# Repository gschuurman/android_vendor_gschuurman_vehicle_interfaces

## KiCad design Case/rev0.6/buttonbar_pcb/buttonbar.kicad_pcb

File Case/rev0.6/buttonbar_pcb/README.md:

# Button bar PCB (case rev 0.6)

Small 2-layer board (176.7 x 11.5 mm) that sits behind the 9 caps of the case's button bar.
Everything goes over the existing **J12** connector on the rev 0.6 main board (5 wires, no main-board change).

Files: `buttonbar.kicad_pro/.kicad_sch/.kicad_pcb` (open in KiCad 7 or newer), project footprint
library `buttonbar.pretty` (all footprints included, no global libraries needed), `buttonbar_schematic.pdf`,
`gerbers/` + `buttonbar_gerbers.zip` (JLCPCB-ready, 2 layers, 1.6 mm), `render/`, `scripts/` (generators).

Status: schematic netlist matches the PCB 1:1 (10 nets), KiCad DRC 0 errors, 0 warnings, 0 unconnected.

## How it works (diode coding)

Every J12 line has a 1k series resistor, a 10k pull-up and 100 nF on the main board.
Single buttons short one line to GND. Combo buttons pull two lines low through two BAT85 Schottky diodes.

| Button | J12 lines low |
|---|---|
| Screen off | 1 (S, GPIO18) |
| Vol + | 2 (U, GPIO17) |
| Vol - | 3 (D, GPIO22) |
| Mute | 4 (M, GPIO16) |
| Play/Pause | 2 + 3 |
| Prev | 3 + 4 |
| Next | 2 + 4 |
| Home | 1 + 3 |
| Voice | 1 + 2 |
| (spare code) | 1 + 4 |

Firmware: wait ~30 ms after the first line goes low, then read all four lines and decode the pattern.
The current firmware treats the lines as four separate buttons, so it needs this decode step.

## Build notes

- **BAT85 (or BAT43) only.** A 1N4148 leaves the line at about 0.8 V, right at the RP2350 VIL limit.
  The cathode band goes on the pad marked K (the square pad).
- **Switch pitch is assumed** at 5.08 mm, 2 pins, body 6 x 3.5 mm, 5 mm high (KW-1556 / Adafruit 1489 type; no
  drawing could be downloaded). Measure yours before ordering. If they differ, change the footprint in
  `buttonbar.pretty` and `btn_total_h` / `btn_body` in the case.
- **J1 = J12 pin for pin** (1 S, 2 U, 3 D, 4 M, 5 GND). There is only 3 mm behind the board in the bar,
  so a pin header does not fit: solder the 5 wires straight into the J1 pads from the back and run them
  out through the wire slot in the bar's back wall (case updated: slot now x -17..-5, support rib moved to x -24
  so it clears J1).
- Switches, diodes and labels are on the front (F) side; solder from the back.
- It needs both copper layers. A single-sided version could not be routed without wire links, so on perfboard
  treat the red (F.Cu) tracks as wire links.

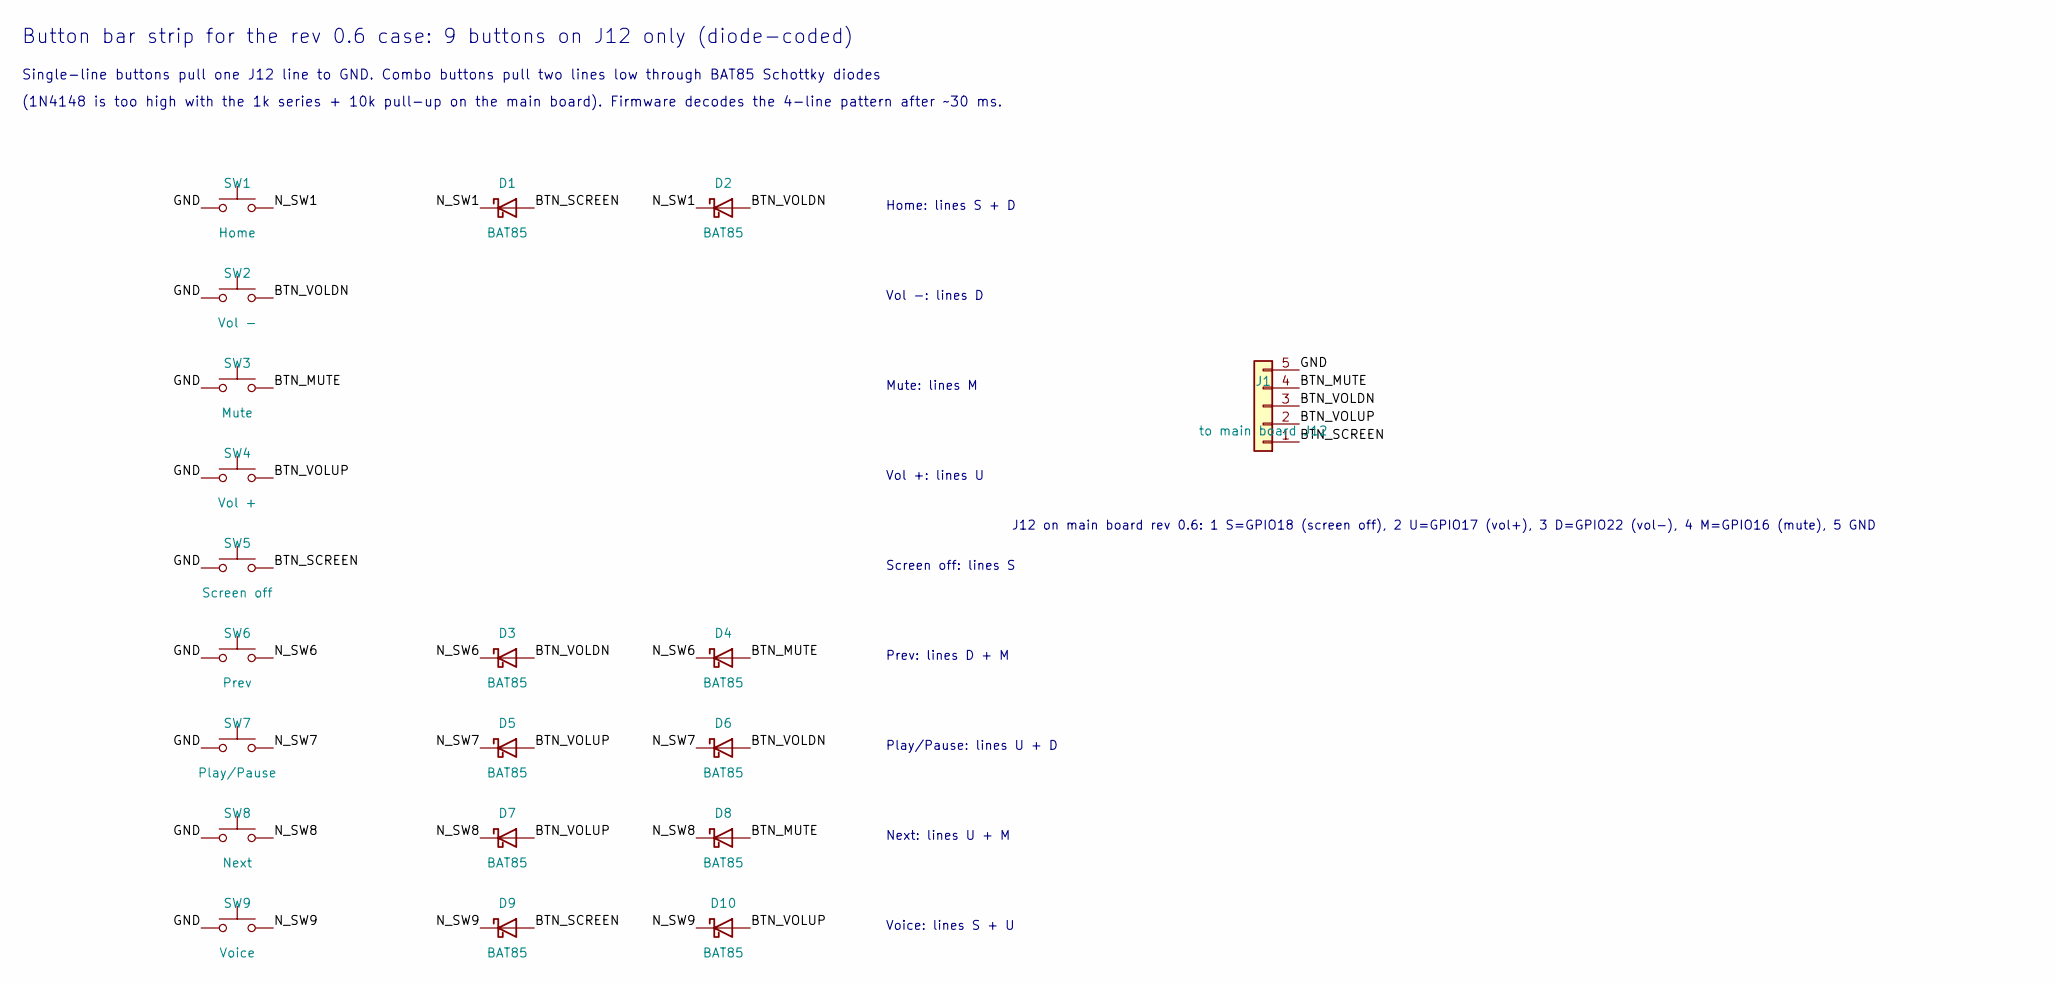
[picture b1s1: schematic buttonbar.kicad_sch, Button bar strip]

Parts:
D1, D2, D3, D4, D5, D6, D7, D8, D9, D10: BAT85; D_DO-34_SOD68_P7.62mm_Horizontal
J1: to main board J12; PinHeader_1x05_P2.54mm_Vertical
SW1: Home; SW_Tactile_6x3.5mm_2pin_P5.08mm
SW2: Vol -; SW_Tactile_6x3.5mm_2pin_P5.08mm
SW3: Mute; SW_Tactile_6x3.5mm_2pin_P5.08mm
SW4: Vol +; SW_Tactile_6x3.5mm_2pin_P5.08mm
SW5: Screen off; SW_Tactile_6x3.5mm_2pin_P5.08mm
SW6: Prev; SW_Tactile_6x3.5mm_2pin_P5.08mm
SW7: Play/Pause; SW_Tactile_6x3.5mm_2pin_P5.08mm
SW8: Next; SW_Tactile_6x3.5mm_2pin_P5.08mm
SW9: Voice; SW_Tactile_6x3.5mm_2pin_P5.08mm

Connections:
/BTN_MUTE: D4.2 (A), D8.2 (A), J1.4, SW3.2
/BTN_SCREEN: D1.2 (A), D9.2 (A), J1.1, SW5.2
/BTN_VOLDN: D2.2 (A), D3.2 (A), D6.2 (A), J1.3, SW2.2
/BTN_VOLUP: D5.2 (A), D7.2 (A), D10.2 (A), J1.2, SW4.2
/N_SW1: D1.1 (K), D2.1 (K), SW1.2
/N_SW6: D3.1 (K), D4.1 (K), SW6.2
/N_SW7: D5.1 (K), D6.1 (K), SW7.2
/N_SW8: D7.1 (K), D8.1 (K), SW8.2
/N_SW9: D9.1 (K), D10.1 (K), SW9.2
GND: J1.5, SW1.1, SW2.1, SW3.1, SW4.1, SW5.1, SW6.1, SW7.1, SW8.1, SW9.1

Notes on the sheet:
Button bar strip for the rev 0.6 case: 9 buttons on J12 only (diode-coded)
Single-line buttons pull one J12 line to GND. Combo buttons pull two lines low through BAT85 Schottky diodes
(1N4148 is too high with the 1k series + 10k pull-up on the main board). Firmware decodes the 4-line pattern after ~30 ms.
Home: lines S + D
Vol -: lines D
Mute: lines M
Vol +: lines U
Screen off: lines S
Prev: lines D + M
Play/Pause: lines U + D
Next: lines U + M
Voice: lines S + U
J12 on main board rev 0.6: 1 S=GPIO18 (screen off), 2 U=GPIO17 (vol+), 3 D=GPIO22 (vol-), 4 M=GPIO16 (mute), 5 GND

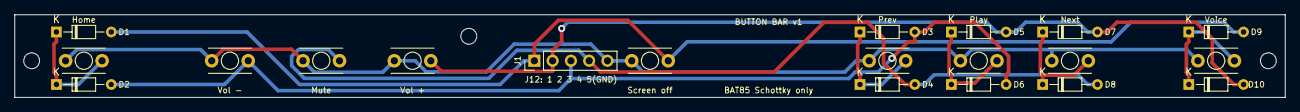
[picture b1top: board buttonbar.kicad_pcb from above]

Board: 2 copper layers, 176.7 x 11.5 mm, 23 parts (0 on the bottom side), 10 nets.

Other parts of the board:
H1, H2, H3: M2 hole; MountingHole_2.2mm_M2

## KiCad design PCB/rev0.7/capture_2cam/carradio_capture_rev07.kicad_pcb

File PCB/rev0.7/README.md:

# PCB rev 0.7: two-camera capture

Rev 0.7 only changes the USB module and adds a capture module, in two versions: `capture_1cam/` (one camera)
and `capture_2cam/` (two cameras). Both plug into the same J29 socket on the USB module; build one of them. The main, audio and
GNSS boards stay at rev 0.6.

## Two-camera capture module (`capture_2cam/`)

Two MacroSilicon MS2107 (LCSC C42374499, LQFP-48), one per camera: analog CVBS in, USB 2.0 UVC out,
behind a CH334R 4-port hub (U10, C4154405) so both share the USB module's single J29 port. Android sees two
normal external cameras (default VID:PID 534d:0021 each), so no driver is needed. The RearViewCamera app
currently opens the first external camera; it needs a setting (or a USB-path match) to pick the reverse one.

- 36 x 67.5 mm, 2 layers. Same outline and H1 as the USB module, extended 12.5 mm downward to the main board's
  bottom edge (the USB module's right edge is already the main board edge).
- J1 (CAM1) and J101 (CAM2): JST PH 2-pin video in (1 = CVBS, 2 = GND), each with 75 ohm termination, 47 nF
  coupling and a USBLC6 ESD clamp.
- J2: 2x3 2.54 mm male header on the bottom side, plugs into USB module J29 and feeds the hub upstream.
- Hub port 1 camera 1, port 2 camera 2, port 3 to J3 (1x4 pads, not fitted: 5 V, D-, D+, GND) for an
  optional third capture board or a test device, port 4 unused.
- Each channel: 12 MHz crystal, internal LDOs, status LED (D1/D101). EEPROMs U3/U103 and R5/R105 are DNP and
  sit on the underside; fit one only to give a camera its own USB name/IDs (ms-tools).
- Routed, DRC 0 unconnected, no copper errors (silkscreen warnings only; H1 is a board-only part).
- Each camera's own 12 V still comes from the reverse-lamp (or other) feed, not from this board.

### How many cameras

Each MS2107 sends uncompressed YUV, about 21 MB/s per PAL/NTSC camera. Everything shares the VIM3 header's
single USB 2.0 High Speed link, which can reserve about 48 MB/s for video, so two cameras can stream at once
(about 41 MB/s) with the RTL-SDR (about 5 MB/s, bulk) still fitting. A third camera on J3 only works if it does
not stream at the same time as the other two. These are calculated numbers, not measured.

### USB pair lengths (mm)

| Pair | D+ | D- |
|---|---|---|
| J2 to hub (upstream; D+ hand-routed on B.Cu between the J2 GND pins) | 12.6 | 10.4 |
| hub to camera 1 | 33.1 | 32.3 |
| hub to camera 2 | 57.1 | 64.8 |
| hub to J3 (not fitted) | 33.2 | 39.0 |

On the USB module D+ is already about 12.7 mm longer than D- (hub 2 to J29), so the upstream skew is about
15 mm in total. Fine for USB 2.0 High Speed in practice; a meander would tidy it if wanted.

## Single-camera capture module (`capture_1cam/`)

The first rev 0.7 board: one MS2107 wired straight to J2, no hub. 36 x 55 mm, the USB module's exact outline.
Same input circuit (J1 JST PH, 75 ohm, 47 nF, USBLC6), optional EEPROM U3/R5 (DNP) on the top side, status
LED D1. Routed, DRC 0 unconnected, no copper errors. USB pair J2 to MS2107: D+ 14.0 mm, D- 10.7 mm; with the
USB module that is about 16 mm of skew in total. Draws about 0.2 A; the 1.1 A F7 covers it too.

## USB module change (`usb/`)

- J29 2x3 female socket (CJT A2541HWV-2x3P, C239343, 8.5 mm body): 1/2 +5V_CAP, 3 D+, 4 D-, 5/6 GND. Wired
  to hub 2 (U14 CH334R) port 4, which was unused. Hub 2 is now full (two phone ports, SDR, capture).
- F7 1.1 A PTC (Bourns MF-NSMF110-2, C89654) feeds +5V_CAP from +5V_SYS, so the capture board only has power
  while the VIM3 is on. Load: hub + two MS2107, about 0.5 A.
- One B.Cu GND track near J29 removed; GND still reaches everything via the pours.
- DRC 0 unconnected, no copper errors. All rev 0.6 symbol UUIDs unchanged.

## Stack

The capture board sits about 11 mm above the USB module (8.5 mm socket + 2.5 mm header spacer), clear of the
USB-A sockets. Use an M2.5 x 11 standoff at H1 on top of the USB module's H1 standoff. Check the USB-A socket
height on the real parts before ordering. The extra 12.5 mm overhangs the main board's bottom strip above the
display-button (J12) and light-sensor (J7) plugs, about 22 mm up; leave room for their wires to bend.

## Regenerating

- `layout/capture_gen_1cam.py` / `capture_gen_2cam.py` write the capture schematics and BOMs (2cam: one `channel(k)`
  per camera, nets CAMk_*, refs +100 for camera 2). Run them inside the matching folder.
- `layout/gen7.py usb` writes the USB module schematic (new parts appended at the end
  so rev 0.6 UUIDs stay put).
- `layout/usb07.py` / `usb07_post.py` and `capture_pcb_1cam.py` / `capture_pcb_2cam.py` / `capture_post.py` do
  placement and post-Freerouting cleanup (KiCad 10 pcbnew Python).

## Bring-up wizards

Step-by-step bench wizards (multimeter first, then first power): `usb/WIZARD.html`, `audio/WIZARD.html`,
`capture_1cam/WIZARD.html` and `capture_2cam/WIZARD.html`. See `../wizard/README.md`.

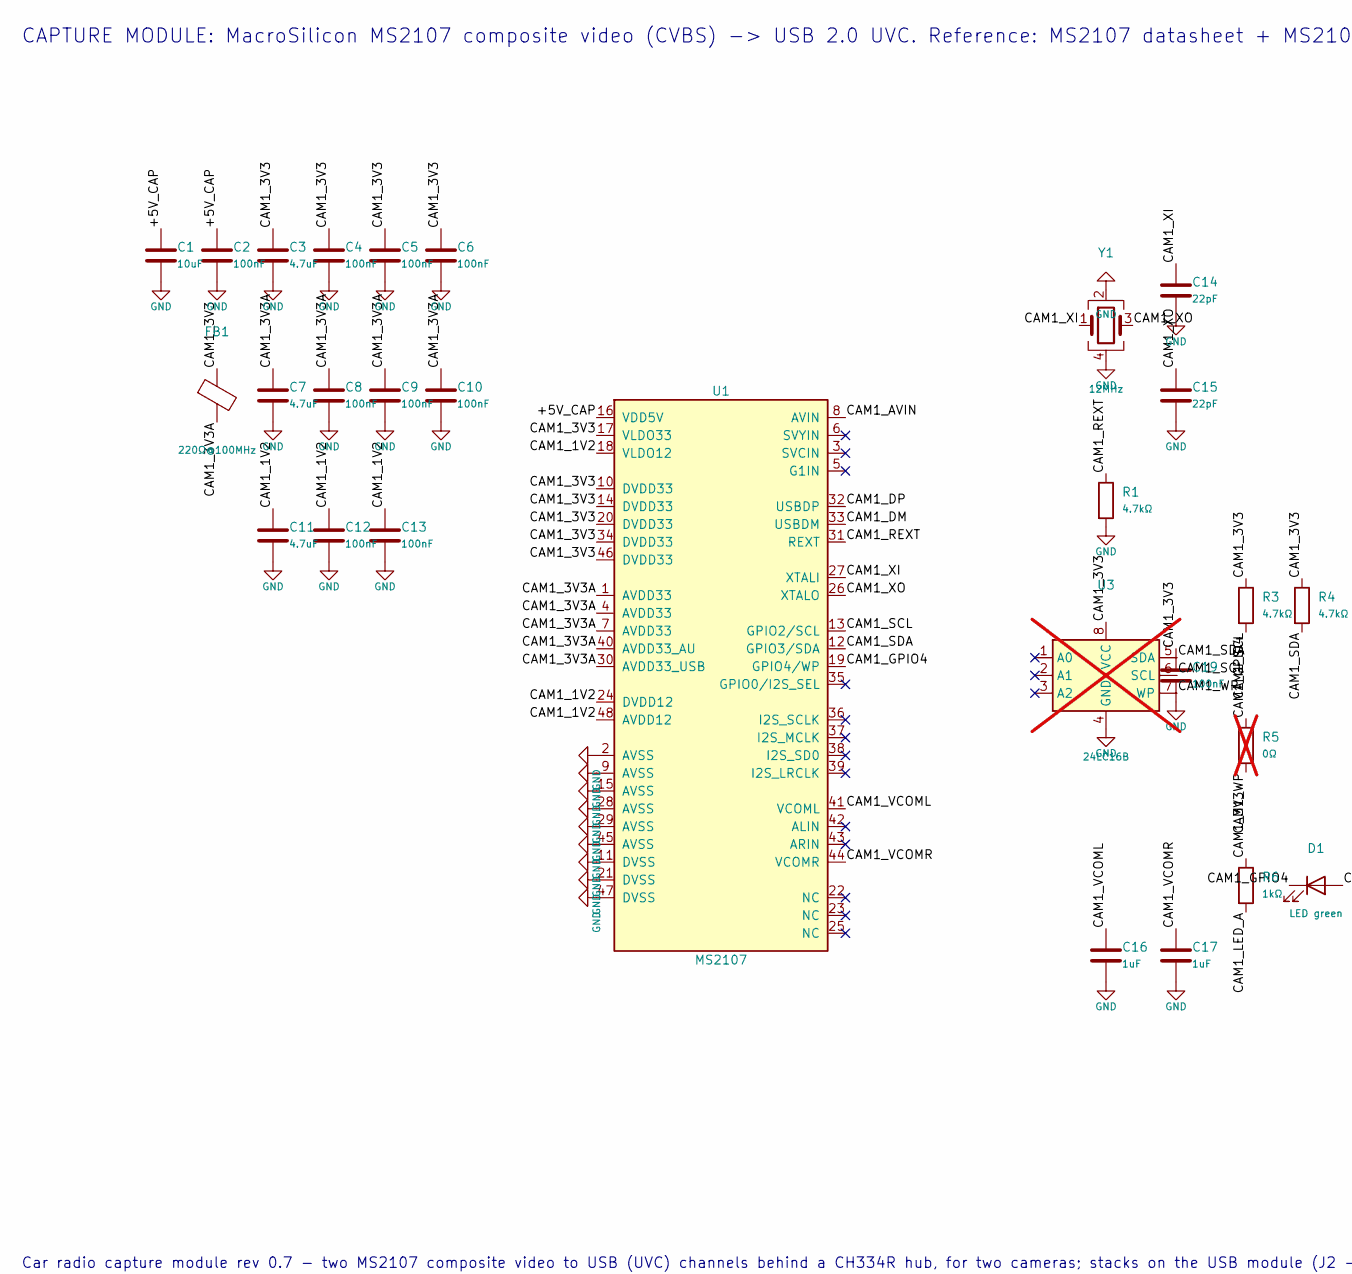
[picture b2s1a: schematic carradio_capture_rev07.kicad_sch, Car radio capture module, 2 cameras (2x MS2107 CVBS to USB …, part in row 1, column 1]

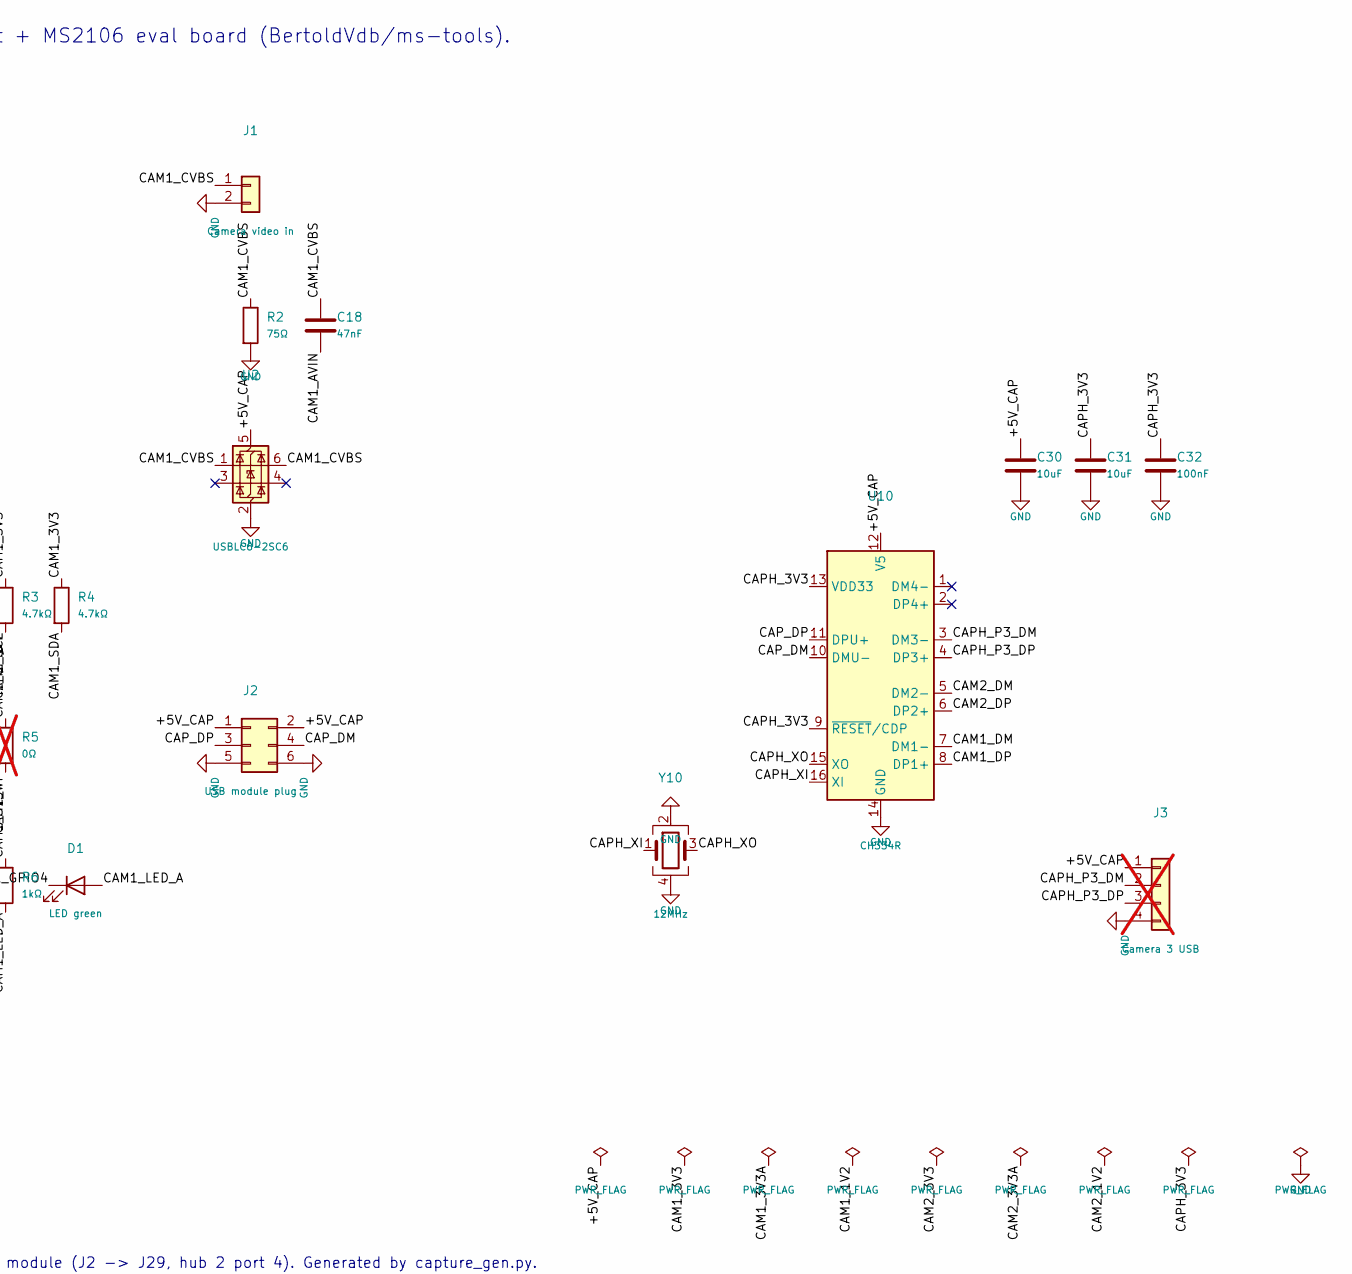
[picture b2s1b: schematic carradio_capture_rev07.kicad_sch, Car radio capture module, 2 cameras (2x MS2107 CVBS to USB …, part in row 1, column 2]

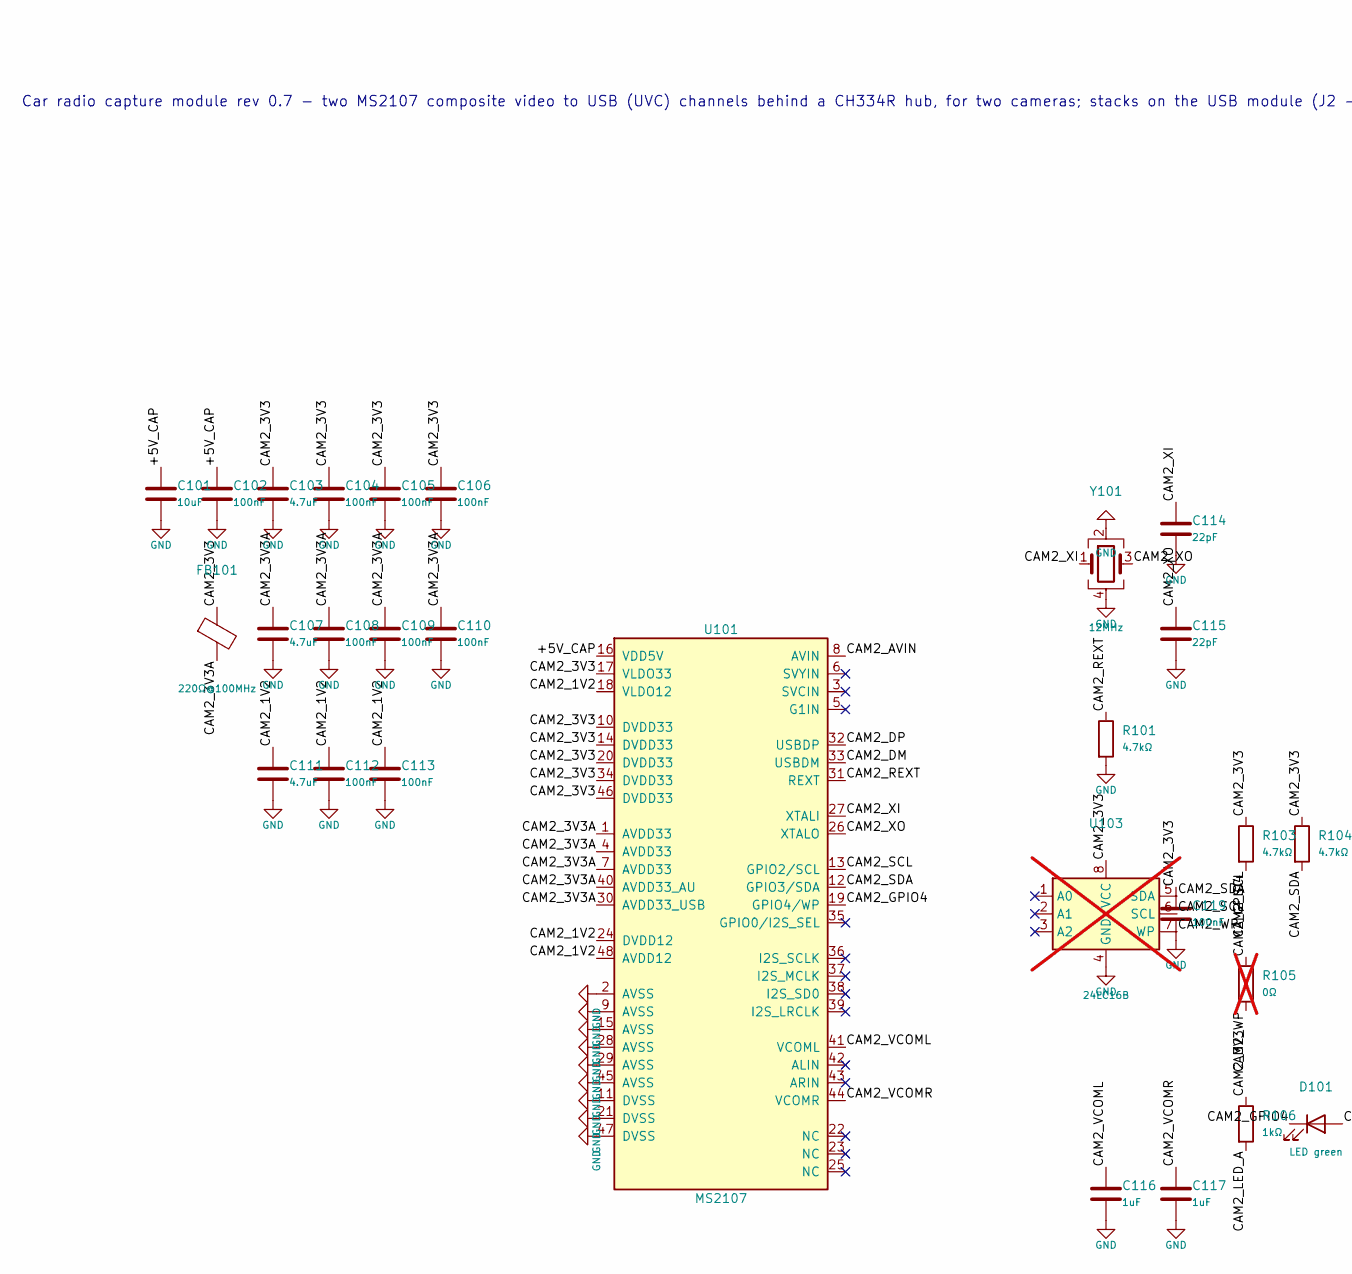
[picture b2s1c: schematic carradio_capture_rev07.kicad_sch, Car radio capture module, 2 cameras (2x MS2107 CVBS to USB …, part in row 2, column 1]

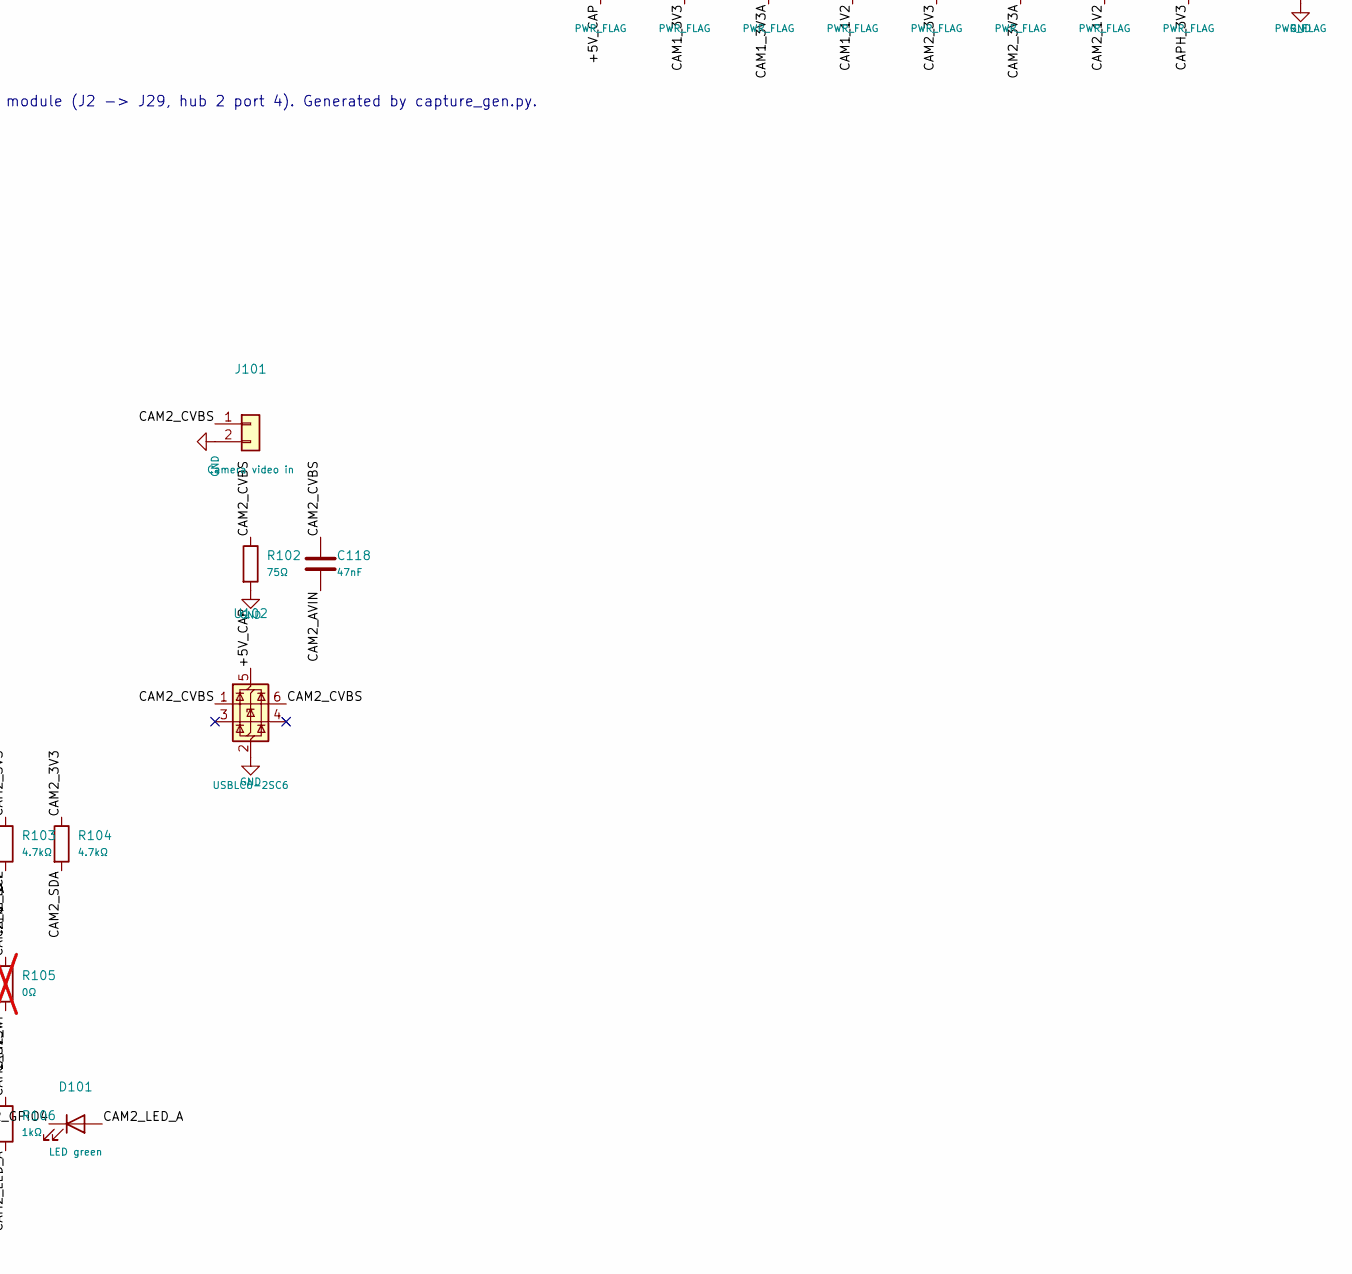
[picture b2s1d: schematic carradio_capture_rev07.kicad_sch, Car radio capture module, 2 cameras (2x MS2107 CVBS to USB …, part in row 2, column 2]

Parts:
C1, C30, C31, C101: 10uF; C_0805_2012Metric; MPN Samsung CL21A106KAYNNNE 0805 10uF 25V X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; LCSC C15850
C2, C4, C5, C6, C8, C9, C10, C12, C13, C19, C32, C102, C104, C105, C106, C108, C109, C110, C112, C113, C119: 100nF; C_0603_1608Metric; MPN YAGEO CC0603KRX7R9BB104 0603 100nF 50V 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; LCSC C14663
C3, C7, C11, C103, C107, C111: 4.7uF; C_0603_1608Metric; MPN Samsung CL10A475KO8NNNC 0603 4.7uF 16V 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; LCSC C19666
C14, C15, C114, C115: 22pF; C_0603_1608Metric; MPN 0603 22pF 50V C0G; LCSC C1653
C16, C17, C116, C117: 1uF; C_0603_1608Metric; MPN Murata GRM188R61H105KAALD 0603 1uF 50V 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; LCSC C77386
C18, C118: 47nF; C_0603_1608Metric; MPN Samsung CL10B473KB8NNNC 0603 47nF 50V X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; LCSC C1622
D1, D101: LED green; LED_0805_2012Metric; MPN KT-0805G green LED; LCSC C2297
FB1, FB101: 220Ω@100MHz; L_0603_1608Metric; MPN Murata BLM18PG221SN1D 0603 ferrite 1.4A; LCSC C80165
J1, J101: Camera video in; JST_PH_B2B-PH-K_1x02_P2.00mm_Vertical; MPN JST B2B-PH-K-S; LCSC C131337
J2: USB module plug; PinHeader_2x03_P2.54mm_Vertical; MPN XFCN PZ254V-12-6P 2x3 2.54mm male heade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; LCSC C492420
J3: Camera 3 USB; PinHeader_1x04_P2.54mm_Vertical; MPN 1x4 2.54mm header, not fitted; not fitted
R1, R3, R4, R101, R103, R104: 4.7kΩ; R_0603_1608Metric; MPN UNI-ROYAL 0603WAF4701T5E 4.7k 1%; LCSC C23162
R2, R102: 75Ω; R_0603_1608Metric; MPN UNI-ROYAL 0603WAF750JT5E 75R 1%; LCSC C4275
R5, R105: 0Ω; R_0603_1608Metric; MPN UNI-ROYAL 0603WAF0000T5E 0R; LCSC C21189; not fitted
R6, R106: 1kΩ; R_0603_1608Metric; MPN UNI-ROYAL 0603WAF1001T5E 1k 1%; LCSC C21190
U1, U101: MS2107; LQFP-48_7x7mm_P0.5mm; MPN MacroSilicon MS2107 CVBS/S-Video to USB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; LCSC C42374499
U2, U102: USBLC6-2SC6; SOT-23-6; MPN ST USBLC6-2SC6; LCSC C7519
U3, U103: 24LC16B; SOIC-8_3.9x4.9mm_P1.27mm; MPN Microchip 24LC16B-I/SN; LCSC C1349383; not fitted
U10: CH334R; QSOP-16_3.9x4.9mm_P0.635mm; MPN WCH CH334R 4-port USB 2.0 hub, QSOP-16; LCSC C4154405
Y1, Y10, Y101: 12MHz; Crystal_SMD_3225-4Pin_3.2x2.5mm; MPN YXC X322512MSB4SI 12MHz 3225; LCSC C9002

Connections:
/+5V_CAP: C1.1, C2.1, C30.1, C101.1, C102.1, J2.1, J2.2, J3.1, U1.16 (VDD5V), U2.5 (VBUS), U10.12 (V5), U101.16 (VDD5V), U102.5 (VBUS)
/CAM1_1V2: C11.1, C12.1, C13.1, U1.18 (VLDO12), U1.24 (DVDD12), U1.48 (AVDD12)
/CAM1_3V3: C3.1, C4.1, C5.1, C6.1, C19.1, FB1.1, R3.1, R4.1, R6.1, U1.10 (DVDD33), U1.14 (DVDD33), U1.17 (VLDO33), U1.20 (DVDD33), U1.34 (DVDD33), U1.46 (DVDD33), U3.8 (VCC)
/CAM1_3V3A: C7.1, C8.1, C9.1, C10.1, FB1.2, U1.1 (AVDD33), U1.4 (AVDD33), U1.7 (AVDD33), U1.30 (AVDD33_USB), U1.40 (AVDD33_AU)
/CAM1_AVIN: C18.2, U1.8 (AVIN)
/CAM1_CVBS: C18.1, J1.1, R2.1, U2.1 (I/O1), U2.6 (I/O1)
/CAM1_DM: U1.33 (USBDM), U10.7 (DM1-)
/CAM1_DP: U1.32 (USBDP), U10.8 (DP1+)
/CAM1_GPIO4: D1.1 (K), R5.1, U1.19 (GPIO4/WP)
/CAM1_LED_A: D1.2 (A), R6.2
/CAM1_REXT: R1.1, U1.31 (REXT)
/CAM1_SCL: R3.2, U1.13 (GPIO2/SCL), U3.6 (SCL)
/CAM1_SDA: R4.2, U1.12 (GPIO3/SDA), U3.5 (SDA)
/CAM1_VCOML: C16.1, U1.41 (VCOML)
/CAM1_VCOMR: C17.1, U1.44 (VCOMR)
/CAM1_WP: R5.2, U3.7 (WP)
/CAM1_XI: C14.1, U1.27 (XTALI), Y1.1
/CAM1_XO: C15.1, U1.26 (XTALO), Y1.3
/CAM2_1V2: C111.1, C112.1, C113.1, U101.18 (VLDO12), U101.24 (DVDD12), U101.48 (AVDD12)
/CAM2_3V3: C103.1, C104.1, C105.1, C106.1, C119.1, FB101.1, R103.1, R104.1, R106.1, U101.10 (DVDD33), U101.14 (DVDD33), U101.17 (VLDO33), U101.20 (DVDD33), U101.34 (DVDD33), U101.46 (DVDD33), U103.8 (VCC)
/CAM2_3V3A: C107.1, C108.1, C109.1, C110.1, FB101.2, U101.1 (AVDD33), U101.4 (AVDD33), U101.7 (AVDD33), U101.30 (AVDD33_USB), U101.40 (AVDD33_AU)
/CAM2_AVIN: C118.2, U101.8 (AVIN)
/CAM2_CVBS: C118.1, J101.1, R102.1, U102.1 (I/O1), U102.6 (I/O1)
/CAM2_DM: U10.5 (DM2-), U101.33 (USBDM)
/CAM2_DP: U10.6 (DP2+), U101.32 (USBDP)
/CAM2_GPIO4: D101.1 (K), R105.1, U101.19 (GPIO4/WP)
/CAM2_LED_A: D101.2 (A), R106.2
/CAM2_REXT: R101.1, U101.31 (REXT)
/CAM2_SCL: R103.2, U101.13 (GPIO2/SCL), U103.6 (SCL)
/CAM2_SDA: R104.2, U101.12 (GPIO3/SDA), U103.5 (SDA)
/CAM2_VCOML: C116.1, U101.41 (VCOML)
/CAM2_VCOMR: C117.1, U101.44 (VCOMR)
/CAM2_WP: R105.2, U103.7 (WP)
/CAM2_XI: C114.1, U101.27 (XTALI), Y101.1
/CAM2_XO: C115.1, U101.26 (XTALO), Y101.3
/CAPH_3V3: C31.1, C32.1, U10.9 (~RESET/CDP), U10.13 (VDD33)
/CAPH_P3_DM: J3.2, U10.3 (DM3-)
/CAPH_P3_DP: J3.3, U10.4 (DP3+)
/CAPH_XI: U10.16 (XI), Y10.1
/CAPH_XO: U10.15 (XO), Y10.3
/CAP_DM: J2.4, U10.10 (DMU-)
/CAP_DP: J2.3, U10.11 (DPU+)
GND: C1.2, C2.2, C3.2, C4.2, C5.2, C6.2, C7.2, C8.2, C9.2, C10.2, C11.2, C12.2, C13.2, C14.2, C15.2, C16.2, C17.2, C19.2, C30.2, C31.2, C32.2, C101.2, C102.2, C103.2, C104.2, C105.2, C106.2, C107.2, C108.2, C109.2, C110.2, C111.2, C112.2, C113.2, C114.2, C115.2, C116.2, C117.2, C119.2, J1.2, J2.5, J2.6, J3.4, J101.2, R1.2, R2.2, R101.2, R102.2, U1.2 (AVSS), U1.9 (AVSS), U1.11 (DVSS), U1.15 (AVSS), U1.21 (DVSS), U1.28 (AVSS), U1.29 (AVSS), U1.45 (AVSS), U1.47 (DVSS), U2.2 (GND), U3.4 (GND), U10.14 (GND), U101.2 (AVSS), U101.9 (AVSS), U101.11 (DVSS), U101.15 (AVSS), U101.21 (DVSS), U101.28 (AVSS), U101.29 (AVSS), U101.45 (AVSS), U101.47 (DVSS), U102.2 (GND), U103.4 (GND), Y1.2, Y1.4, Y10.2, Y10.4, Y101.2, Y101.4; also elsewhere on the board

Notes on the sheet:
CAPTURE MODULE: MacroSilicon MS2107 composite video (CVBS) -> USB 2.0 UVC. Reference: MS2107 datasheet + MS2106 eval board (BertoldVdb/ms-tools).
Car radio capture module rev 0.7 - two MS2107 composite video to USB (UVC) channels behind a CH334R hub, for two cameras; stacks on the USB module (J2 -> J29, hub 2 port 4). Generated by capture_gen.py.

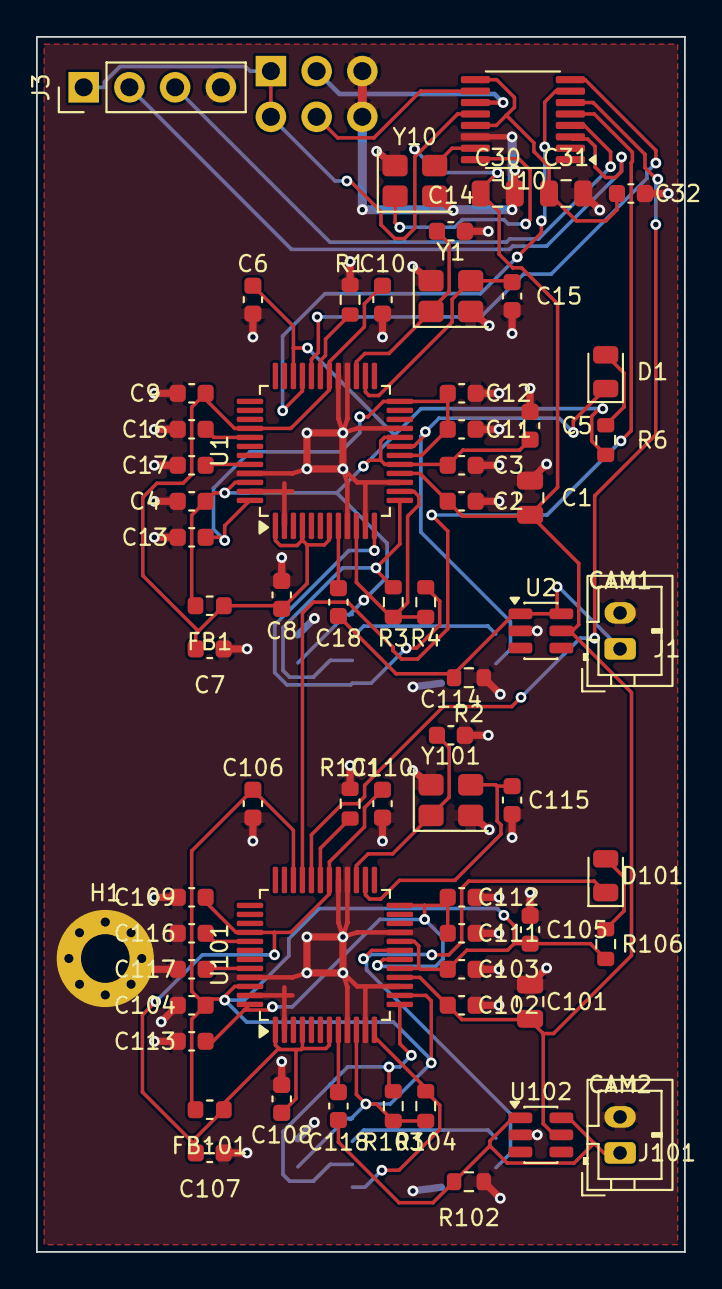
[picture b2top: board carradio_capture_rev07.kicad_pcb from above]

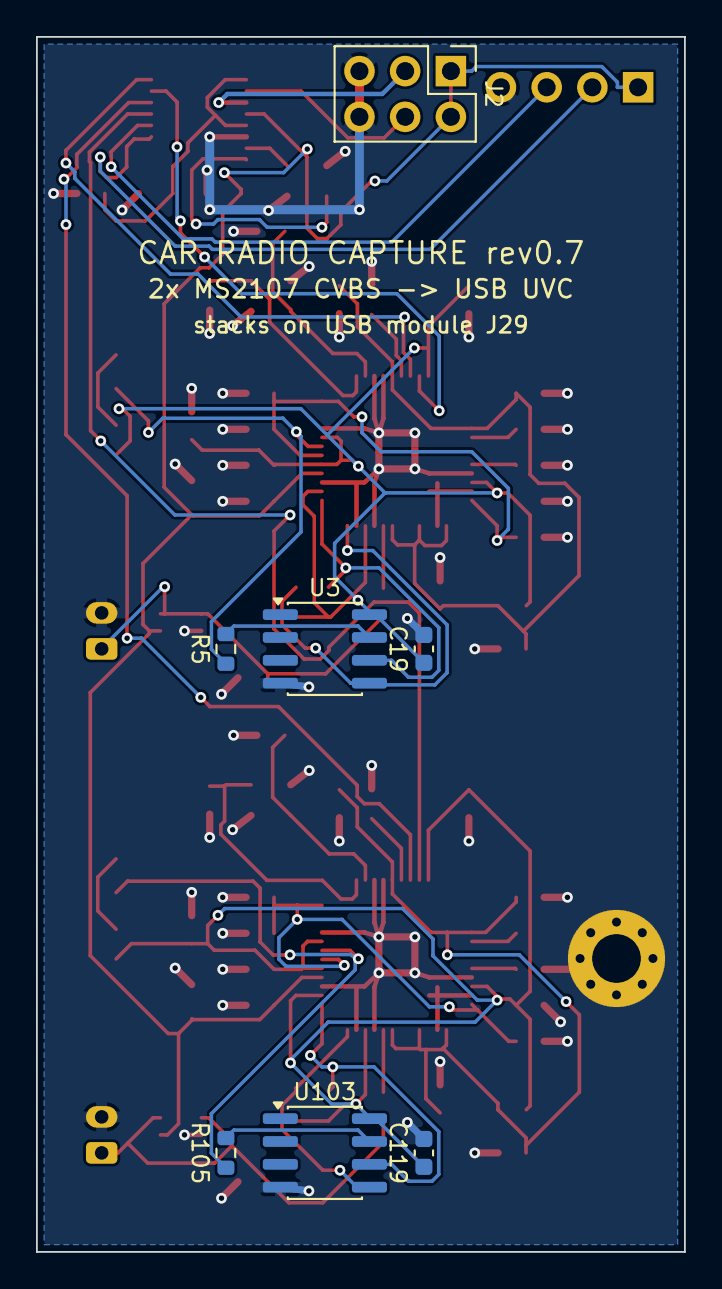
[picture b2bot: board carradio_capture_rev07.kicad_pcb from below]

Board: 2 copper layers, 36.0 x 67.5 mm, 72 parts (7 on the bottom side), 43 nets.

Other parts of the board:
H1: MountingHole_2.7mm_M2.5_Pad_Via

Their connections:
GND: H1.1; also elsewhere on the board

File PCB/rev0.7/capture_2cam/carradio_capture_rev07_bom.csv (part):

Designator,Value,Description / MPN,LCSC,Footprint (KiCad name),Fit,Note
J2,USB module plug,XFCN PZ254V-12-6P 2x3 2.54mm male header (underside),C492420,Connector_PinHeader_2.54mm:PinHeader_2x03_P2.54mm_Vertical,yes,plugs into the 2x3 socket on the USB module: hub 2 port 4 and its own 1 A PTC from +5V_SYS; feeds the on-board hub U10
U1,MS2107,"MacroSilicon MS2107 CVBS/S-Video to USB 2.0 UVC capture, LQFP-48 7x7 0.5mm",C42374499,Package_QFP:LQFP-48_7x7mm_P0.5mm,yes,"UVC 1.0 / UAC 1.0, no driver needed; YUV422 720x576/480 or MJPEG; 0-70 C rated. SVYIN/SVCIN/G1IN, I2S and line-in unused (open). GPIO0 open = internal audio ADC (default)"
C1,10uF,Samsung CL21A106KAYNNNE 0805 10uF 25V X5R,C15850,Capacitor_SMD:C_0805_2012Metric,yes,bulk at the module plug
C2,100nF,YAGEO CC0603KRX7R9BB104 0603 100nF 50V X7R,C14663,Capacitor_SMD:C_0603_1608Metric,yes,at pin 16
C3,4.7uF,Samsung CL10A475KO8NNNC 0603 4.7uF 16V X5R,C19666,Capacitor_SMD:C_0603_1608Metric,yes,VLDO33 output cap at pin 17
C4,100nF,YAGEO CC0603KRX7R9BB104 0603 100nF 50V X7R,C14663,Capacitor_SMD:C_0603_1608Metric,yes,DVDD33 pins 10/14
C5,100nF,YAGEO CC0603KRX7R9BB104 0603 100nF 50V X7R,C14663,Capacitor_SMD:C_0603_1608Metric,yes,DVDD33 pins 20/34
C6,100nF,YAGEO CC0603KRX7R9BB104 0603 100nF 50V X7R,C14663,Capacitor_SMD:C_0603_1608Metric,yes,DVDD33 pin 46
FB1,220Ω@100MHz,Murata BLM18PG221SN1D 0603 ferrite 1.4A,C80165,Inductor_SMD:L_0603_1608Metric,yes,"separates the analog 3.3 V (video/audio ADC, USB PHY) from the digital 3.3 V"
C7,4.7uF,Samsung CL10A475KO8NNNC 0603 4.7uF 16V X5R,C19666,Capacitor_SMD:C_0603_1608Metric,yes,
C8,100nF,YAGEO CC0603KRX7R9BB104 0603 100nF 50V X7R,C14663,Capacitor_SMD:C_0603_1608Metric,yes,AVDD33 pins 1/4
C9,100nF,YAGEO CC0603KRX7R9BB104 0603 100nF 50V X7R,C14663,Capacitor_SMD:C_0603_1608Metric,yes,AVDD33 pin 7 / AVDD33_AU pin 40
C10,100nF,YAGEO CC0603KRX7R9BB104 0603 100nF 50V X7R,C14663,Capacitor_SMD:C_0603_1608Metric,yes,AVDD33_USB pin 30
C11,4.7uF,Samsung CL10A475KO8NNNC 0603 4.7uF 16V X5R,C19666,Capacitor_SMD:C_0603_1608Metric,yes,VLDO12 output cap at pin 18
C12,100nF,YAGEO CC0603KRX7R9BB104 0603 100nF 50V X7R,C14663,Capacitor_SMD:C_0603_1608Metric,yes,DVDD12 pin 24
C13,100nF,YAGEO CC0603KRX7R9BB104 0603 100nF 50V X7R,C14663,Capacitor_SMD:C_0603_1608Metric,yes,AVDD12 pin 48
Y1,12MHz,YXC X322512MSB4SI 12MHz 3225,C9002,Crystal:Crystal_SMD_3225-4Pin_3.2x2.5mm,yes,same crystal as the hubs
C14,22pF,0603 22pF 50V C0G,C1653,Capacitor_SMD:C_0603_1608Metric,yes,load cap (eval board: 10 pF with its crystal; 22 pF suits the 20 pF-load X322512MSB4SI)
C15,22pF,0603 22pF 50V C0G,C1653,Capacitor_SMD:C_0603_1608Metric,yes,
R1,4.7kΩ,UNI-ROYAL 0603WAF4701T5E 4.7k 1%,C23162,Resistor_SMD:R_0603_1608Metric,yes,REXT 4.7k 1% to GND (datasheet)
C16,1uF,Murata GRM188R61H105KAALD 0603 1uF 50V X5R,C77386,Capacitor_SMD:C_0603_1608Metric,yes,audio ADC reference decoupling (eval board); line-in itself unused
C17,1uF,Murata GRM188R61H105KAALD 0603 1uF 50V X5R,C77386,Capacitor_SMD:C_0603_1608Metric,yes,
J1,Camera video in,JST B2B-PH-K-S,C131337,Connector_JST:JST_PH_B2B-PH-K_1x02_P2.00mm_Vertical,yes,"pin 1 camera video (RCA centre), pin 2 camera video ground (RCA shell); lead to an RCA socket. Camera 12 V comes from the reverse lamp as usual"
R2,75Ω,UNI-ROYAL 0603WAF750JT5E 75R 1%,C4275,Resistor_SMD:R_0603_1608Metric,yes,75 ohm line termination
C18,47nF,Samsung CL10B473KB8NNNC 0603 47nF 50V X7R,C1622,Capacitor_SMD:C_0603_1608Metric,yes,AC coupling into AVIN (pin 8)
U2,USBLC6-2SC6,ST USBLC6-2SC6,C7519,Package_TO_SOT_SMD:SOT-23-6,yes,"ESD on the camera line (car wiring); one channel, pass the trace straight through pins 1-6"
U3,24LC16B,Microchip 24LC16B-I/SN,C1349383,Package_SO:SOIC-8_3.9x4.9mm_P1.27mm,DNP,"optional, not fitted: without it the MS2107 enumerates as 534d:0021 'USB Video' with the default modes. Fit to customise via ms-tools"
C19,100nF,YAGEO CC0603KRX7R9BB104 0603 100nF 50V X7R,C14663,Capacitor_SMD:C_0603_1608Metric,yes,EEPROM decoupling
R3,4.7kΩ,UNI-ROYAL 0603WAF4701T5E 4.7k 1%,C23162,Resistor_SMD:R_0603_1608Metric,yes,I2C pull-ups keep GPIO2/3 defined with or without the EEPROM
R4,4.7kΩ,UNI-ROYAL 0603WAF4701T5E 4.7k 1%,C23162,Resistor_SMD:R_0603_1608Metric,yes,
R5,0Ω,UNI-ROYAL 0603WAF0000T5E 0R,C21189,Resistor_SMD:R_0603_1608Metric,DNP,eval board option: WP from GPIO4; open = WP held low inside the 24LC16B (writable)
R6,1kΩ,UNI-ROYAL 0603WAF1001T5E 1k 1%,C21190,Resistor_SMD:R_0603_1608Metric,yes,
D1,LED green,KT-0805G green LED,C2297,LED_SMD:LED_0805_2012Metric,yes,GPIO4 sinks: on while the capture streams (MS2106 eval board behaviour)
U101,MS2107,"MacroSilicon MS2107 CVBS/S-Video to USB 2.0 UVC capture, LQFP-48 7x7 0.5mm",C42374499,Package_QFP:LQFP-48_7x7mm_P0.5mm,yes,"UVC 1.0 / UAC 1.0, no driver needed; YUV422 720x576/480 or MJPEG; 0-70 C rated. SVYIN/SVCIN/G1IN, I2S and line-in unused (open). GPIO0 open = internal audio ADC (default)"
C101,10uF,Samsung CL21A106KAYNNNE 0805 10uF 25V X5R,C15850,Capacitor_SMD:C_0805_2012Metric,yes,bulk at the module plug
C102,100nF,YAGEO CC0603KRX7R9BB104 0603 100nF 50V X7R,C14663,Capacitor_SMD:C_0603_1608Metric,yes,at pin 16
C103,4.7uF,Samsung CL10A475KO8NNNC 0603 4.7uF 16V X5R,C19666,Capacitor_SMD:C_0603_1608Metric,yes,VLDO33 output cap at pin 17
C104,100nF,YAGEO CC0603KRX7R9BB104 0603 100nF 50V X7R,C14663,Capacitor_SMD:C_0603_1608Metric,yes,DVDD33 pins 10/14
C105,100nF,YAGEO CC0603KRX7R9BB104 0603 100nF 50V X7R,C14663,Capacitor_SMD:C_0603_1608Metric,yes,DVDD33 pins 20/34
C106,100nF,YAGEO CC0603KRX7R9BB104 0603 100nF 50V X7R,C14663,Capacitor_SMD:C_0603_1608Metric,yes,DVDD33 pin 46
FB101,220Ω@100MHz,Murata BLM18PG221SN1D 0603 ferrite 1.4A,C80165,Inductor_SMD:L_0603_1608Metric,yes,"separates the analog 3.3 V (video/audio ADC, USB PHY) from the digital 3.3 V"
C107,4.7uF,Samsung CL10A475KO8NNNC 0603 4.7uF 16V X5R,C19666,Capacitor_SMD:C_0603_1608Metric,yes,
C108,100nF,YAGEO CC0603KRX7R9BB104 0603 100nF 50V X7R,C14663,Capacitor_SMD:C_0603_1608Metric,yes,AVDD33 pins 1/4
C109,100nF,YAGEO CC0603KRX7R9BB104 0603 100nF 50V X7R,C14663,Capacitor_SMD:C_0603_1608Metric,yes,AVDD33 pin 7 / AVDD33_AU pin 40
C110,100nF,YAGEO CC0603KRX7R9BB104 0603 100nF 50V X7R,C14663,Capacitor_SMD:C_0603_1608Metric,yes,AVDD33_USB pin 30
C111,4.7uF,Samsung CL10A475KO8NNNC 0603 4.7uF 16V X5R,C19666,Capacitor_SMD:C_0603_1608Metric,yes,VLDO12 output cap at pin 18
C112,100nF,YAGEO CC0603KRX7R9BB104 0603 100nF 50V X7R,C14663,Capacitor_SMD:C_0603_1608Metric,yes,DVDD12 pin 24
C113,100nF,YAGEO CC0603KRX7R9BB104 0603 100nF 50V X7R,C14663,Capacitor_SMD:C_0603_1608Metric,yes,AVDD12 pin 48
Y101,12MHz,YXC X322512MSB4SI 12MHz 3225,C9002,Crystal:Crystal_SMD_3225-4Pin_3.2x2.5mm,yes,same crystal as the hubs
C114,22pF,0603 22pF 50V C0G,C1653,Capacitor_SMD:C_0603_1608Metric,yes,load cap (eval board: 10 pF with its crystal; 22 pF suits the 20 pF-load X322512MSB4SI)
C115,22pF,0603 22pF 50V C0G,C1653,Capacitor_SMD:C_0603_1608Metric,yes,
R101,4.7kΩ,UNI-ROYAL 0603WAF4701T5E 4.7k 1%,C23162,Resistor_SMD:R_0603_1608Metric,yes,REXT 4.7k 1% to GND (datasheet)
C116,1uF,Murata GRM188R61H105KAALD 0603 1uF 50V X5R,C77386,Capacitor_SMD:C_0603_1608Metric,yes,audio ADC reference decoupling (eval board); line-in itself unused
C117,1uF,Murata GRM188R61H105KAALD 0603 1uF 50V X5R,C77386,Capacitor_SMD:C_0603_1608Metric,yes,
J101,Camera video in,JST B2B-PH-K-S,C131337,Connector_JST:JST_PH_B2B-PH-K_1x02_P2.00mm_Vertical,yes,"pin 1 camera video (RCA centre), pin 2 camera video ground (RCA shell); lead to an RCA socket. Camera 12 V comes from the reverse lamp as usual"
R102,75Ω,UNI-ROYAL 0603WAF750JT5E 75R 1%,C4275,Resistor_SMD:R_0603_1608Metric,yes,75 ohm line termination
C118,47nF,Samsung CL10B473KB8NNNC 0603 47nF 50V X7R,C1622,Capacitor_SMD:C_0603_1608Metric,yes,AC coupling into AVIN (pin 8)
U102,USBLC6-2SC6,ST USBLC6-2SC6,C7519,Package_TO_SOT_SMD:SOT-23-6,yes,"ESD on the camera line (car wiring); one channel, pass the trace straight through pins 1-6"
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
